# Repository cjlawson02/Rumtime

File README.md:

# Rumtime

**Rumtime** is a modular cocktail execution engine: ingredients are registered as services, recipes are resolved at runtime, and beverages are dispensed through a scalable ESP32-powered pump architecture.

This repo holds Rumtime documentation, Phase 0 bench-rig firmware, and KiCad PCB specifications. CAD and full product firmware are still in progress. The v1 hardware design uses food-safe tubing, Kamoer KPHM100-class reversible peristaltic pumps, modular 4-pump cartridges, and an ESP32-S3 controller. Software stack direction (Cloudflare kiosk UI, ESP32 dispense engine) and **locked** firmware runtime model (`ControlTask` + command queue on FreeRTOS) are in [`docs/16-firmware-and-software-architecture.md`](docs/16-firmware-and-software-architecture.md). Kiosk UX and **React + shadcn** stack in [`docs/17-kiosk-ui-plan.md`](docs/17-kiosk-ui-plan.md); production app at [`ui/kiosk/`](ui/kiosk/). Provisional device HTTP contract in [`docs/18-kiosk-device-api.md`](docs/18-kiosk-device-api.md).

## Current design snapshot

- **Version 1 pump count:** 8 installed pumps.
- **Expansion target:** 12 total pumps via one additional 4-pump module.
- **Control platform:** ESP32-S3 or similar ESP32 board, Wi-Fi only.
- **Pump strategy:** One reversible peristaltic pump per ingredient.
- **Measurement strategy:** Timed dispensing after calibration; **load cell required** for glass/ice detection, **flow-gated pour start**, and sanity checks.
- **Carbonation:** Do not pump carbonated mixers in v1. Software should instruct the user to top off manually.
- **Cleaning:** Moderate-effort cleaning with warm-water flush and Star San/session sanitizer workflow.
- **Budget target:** About $500 max for v1, excluding liquor and ingredients.
- **Build style:** Finished-looking countertop dispenser, with external bottles and replaceable tubing.

## Document map

| File                                                                                     | Purpose                                                                                        |
| ---------------------------------------------------------------------------------------- | ---------------------------------------------------------------------------------------------- |
| [`AGENTS.md`](AGENTS.md)                                                                 | Coding-agent and contributor behavior rules based on the requested Karpathy-style guidelines.  |
| [`docs/00-project-brief.md`](docs/00-project-brief.md)                                   | Scope, goals, assumptions, and non-goals.                                                      |
| [`docs/01-decisions.md`](docs/01-decisions.md)                                           | All captured design decisions from the planning conversation.                                  |
| [`docs/02-system-architecture.md`](docs/02-system-architecture.md)                       | Hardware architecture and module layout.                                                       |
| [`docs/03-parts-list-bom.md`](docs/03-parts-list-bom.md)                                 | Initial parts list with budget notes and sourcing guidance.                                    |
| [`docs/04-plumbing-and-fluid-path.md`](docs/04-plumbing-and-fluid-path.md)               | Tubing, fittings, bottles, nozzles, and ingredient compatibility.                              |
| [`docs/05-electronics-and-pcb.md`](docs/05-electronics-and-pcb.md)                       | Electrical design and 4-pump PCB guidance.                                                     |
| [`docs/06-flow-calibration-and-inventory.md`](docs/06-flow-calibration-and-inventory.md) | Timed flow calibration, flow-gated dispense, load cell, and inventory tracking.                |
| [`docs/07-cleaning-and-food-safety.md`](docs/07-cleaning-and-food-safety.md)             | Cleaning workflow, sanitizer handling, and maintenance assumptions.                            |
| [`docs/08-mechanical-design.md`](docs/08-mechanical-design.md)                           | Enclosure, pump cartridges, drip tray, nozzle cluster, and fridge notes.                       |
| [`docs/09-build-plan-and-verification.md`](docs/09-build-plan-and-verification.md)       | Staged build plan with success criteria and test checks.                                       |
| [`docs/10-open-questions-and-v2.md`](docs/10-open-questions-and-v2.md)                   | Deferred decisions, v2 ideas, and risks.                                                       |
| [`docs/11-sourcing-notes.md`](docs/11-sourcing-notes.md)                                 | Sourcing notes and search terms for pumps, tubing, fittings, electronics, and enclosure parts. |
| [`docs/12-phase-0-decisions.md`](docs/12-phase-0-decisions.md)                           | Research-backed Phase 0 part decisions (pump, PSU, KiCad).                                     |
| [`docs/13-phase-0-mini-bom.md`](docs/13-phase-0-mini-bom.md)                             | Phase 0 shopping list (~2-pump bench rig).                                                     |
| [`docs/14-bench-test-protocol.md`](docs/14-bench-test-protocol.md)                       | Bench tests, pass criteria, and session log template.                                          |
| [`docs/15-project-timeline.md`](docs/15-project-timeline.md)                             | Gantt chart, milestones, and procurement log (order/receive dates).                            |
| [`docs/16-firmware-and-software-architecture.md`](docs/16-firmware-and-software-architecture.md) | Software stack decisions, firmware layers, sequence runner, NVS ownership, migration from bench rig. |
| [`docs/17-kiosk-ui-plan.md`](docs/17-kiosk-ui-plan.md)                                   | Locked kiosk UX, connectivity, and guest/setup flows.                                          |
| [`ui/kiosk/`](ui/kiosk/)                                                                 | Production kiosk PWA — see [`ui/kiosk/README.md`](ui/kiosk/README.md). |
| [`firmware/bench-rig/`](firmware/bench-rig/)                                             | ESP32-S3 + TB6612 bring-up firmware (PlatformIO).                                              |
| [`firmware/controller/`](firmware/controller/)                                          | ESP32-S3 product firmware scaffold (`ControlTask` runtime; pump subsystem implemented).        |
| [`hardware/kicad/`](hardware/kicad/)                                                     | KiCad 4-pump module project, schematic spec, and `kicad-cli` scripts.                          |
| [`hardware/cad/`](hardware/cad/)                                                         | build123d parametric CAD (`src/`), dimension refs (`refs/`), export scripts; Onshape for assembly review only. |

## Design philosophy

Build the simplest version of Rumtime that can make repeatable drinks, clean up reasonably, and expand without rewiring everything. Avoid premature complexity such as inline flow meters, shared manifolds, fridge drilling, carbonated pumping, or fully custom embedded module networks until the basic 8-pump machine has been validated.

## Current status

**Next action:** Fit-check/measure the assembled load-cell cantilever, then solder the bar to HX711 (E+/E−/A+/A−) and run Tests 7–9. **Parallel:** finish 4-pump **PCB layout** (silkscreen/placement). Schematic v1 is ERC-clean. Bar **75 mm**, holes **5 / 15 / 59 / 69**, **M4 tapped** — [`hardware/cad/refs/estardyn-load-cell.md`](hardware/cad/refs/estardyn-load-cell.md). HX711↔MCU already wired (GPIO 8/9). Sessions: [06](docs/bench-results/2026-08-16-session-06.md) (measure + print) · [07](docs/bench-results/2026-08-16-session-07.md) (assembled, not measured).

**Done so far:** **8× correct 12 V HB pumps are on hand** and the 2 wrong 24 V units were returned. **P1 + P2** are bench-validated @ **1.75 ml/s**; dual-pump **~0.4 A**; anti-drip **100 ms**; P2 sequential 50 ml target → **~45 ml** (anti-drip); host CLI **`benchctl.py`** + proto=2 serial parser. The other 6 pumps still need incoming inspection and variance testing.

Decisions are locked in [`docs/12-phase-0-decisions.md`](docs/12-phase-0-decisions.md) (KPHM100-HBB10 pump, TB6612 breakout, ESP32-S3-DevKitC-1, KiCad for Phase 2 PCB).

## First prototype goal

Validate the core liquid path with 2–4 pumps. **Module schematic v1 is done** (ERC clean). Layout/silkscreen in progress. **Fab** waits on **DRC** (I2C bring-up is Test 10 on the first board).

1. Dispense 15 ml, 30 ml, and 60 ml targets by time after calibration.
2. Validate **flow-gated dispense** vs timed-only on de-primed and post–anti-drip lines (Test 9) — v1 pour default, not a PCB gate.
3. Reverse briefly after pours to reduce drips; document sequential pour drift (Test 4b).
4. Flush simple syrup and grenadine adequately with warm water.
5. Confirm tubing and nozzles do not retain obvious flavor or clog during a normal session.
6. Confirm load cell detects glass, ice tare, flow onset, and no-flow conditions (Tests 7–9) — v1 pour, not a PCB gate.
7. I2C pump control is proven on the **first assembled module** (Test 10), not a pre-fab MCP23017 breakout.

After DRC, fabricate the 4-pump module (`hardware/kicad/`) and proceed to the finished enclosure.

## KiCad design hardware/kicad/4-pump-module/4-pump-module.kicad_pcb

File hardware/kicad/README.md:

# KiCad Hardware

Rumtime PCBs are designed in **KiCad 10**. Bench validation (Phase 0–1) uses breakouts; the first custom board is the **4-pump module** (Phase 2).

Installed on this machine: **KiCad 10.0.5** (`kicad-cli` on PATH via Homebrew).

## Repo layout

```text
hardware/kicad/
  README.md
  4-pump-module-spec.md     — nets, pin map, safe-off (source of truth before symbols)
  4-pump-module/            — KiCad project
  main-controller-spec.md   — motherboard nets / connectors
  main-controller/          — KiCad project
    Rumtime.pretty/           — local footprints (Mini560)
    fp-lib-table
  scripts/
    check.sh                — ERC (+ DRC); default both boards
    export.sh               — PDF / netlist / BOM; --fab for Gerbers
  out/                      — generated (gitignored)
```

## Agent / CLI hook

`kicad-cli` cannot place symbols. Use it to **check and export** after schematic/layout edits in KiCad.

```bash
kicad-cli version
hardware/kicad/scripts/check.sh                       # ERC both boards
hardware/kicad/scripts/check.sh main-controller       # one board
hardware/kicad/scripts/check.sh --drc                 # ERC + DRC (after Edge.Cuts)
hardware/kicad/scripts/export.sh                      # PDF + netlist
hardware/kicad/scripts/export.sh --fab                # Gerbers + drill + STEP
```

Useful one-shots:

```bash
kicad-cli sch erc --exit-code-violations hardware/kicad/4-pump-module/4-pump-module.kicad_sch
kicad-cli sch erc --exit-code-violations hardware/kicad/main-controller/main-controller.kicad_sch
kicad-cli pcb drc --schematic-parity --exit-code-violations hardware/kicad/4-pump-module/4-pump-module.kicad_pcb
kicad-cli sch export pdf --output hardware/kicad/out/sch.pdf hardware/kicad/4-pump-module/4-pump-module.kicad_sch
```

Open the GUI:

```bash
open -a KiCad hardware/kicad/4-pump-module/4-pump-module.kicad_pro
open -a KiCad hardware/kicad/main-controller/main-controller.kicad_pro
```

## Design sequence

| Phase | Board                      | Action                                              |
| ----- | -------------------------- | --------------------------------------------------- |
| 0–1   | None                       | TB6612 breakout on breadboard; HX711 + load cell    |
| 2     | 4-pump module              | First fab — Test 10 I2C bring-up on this board      |
| 4     | Second 4-pump module       | Duplicate validated design                          |
| 5     | Main controller            | PCB ordered 2026-10-29. DevKit socketed. |

Fill schematic sheets per [`4-pump-module-spec.md`](4-pump-module-spec.md) / [`main-controller-spec.md`](main-controller-spec.md). **4-pump** PCB ordered 2026-10-25 (OSH Park). **Main-controller** PCB ordered 2026-10-29. Commit `.kicad_pro` / `.kicad_sch` / `.kicad_pcb` — not `out/` or `*-backups/`.

## Gate before fabrication

HX711 / load cell is on the **ESP32 controller**, not this module. Tests 7–9 do **not** gate schematic or fab.

Do not **order** boards until:

1. Measured pump current (dry and wet stall) recorded in `docs/bench-results/`. _(Done — TB6612 OK.)_
2. `scripts/check.sh` ERC (and DRC) clean. _(ERC done 2026-08-16; DRC after Edge.Cuts.)_
3. Schematic safe-off review (Test 10.4: IN1/IN2 PDs, STBY PD, PWM strap, MCP23017 /RESET).

**Do not** wait on an MCP23017 breakout. Test 10.1–10.3 run on the first assembled module.

Layout may continue now. Phase 1 pour completeness (Tests 4, 6, 7–9, P3) is parallel v1 work — see [`docs/14-bench-test-protocol.md`](../../docs/14-bench-test-protocol.md).

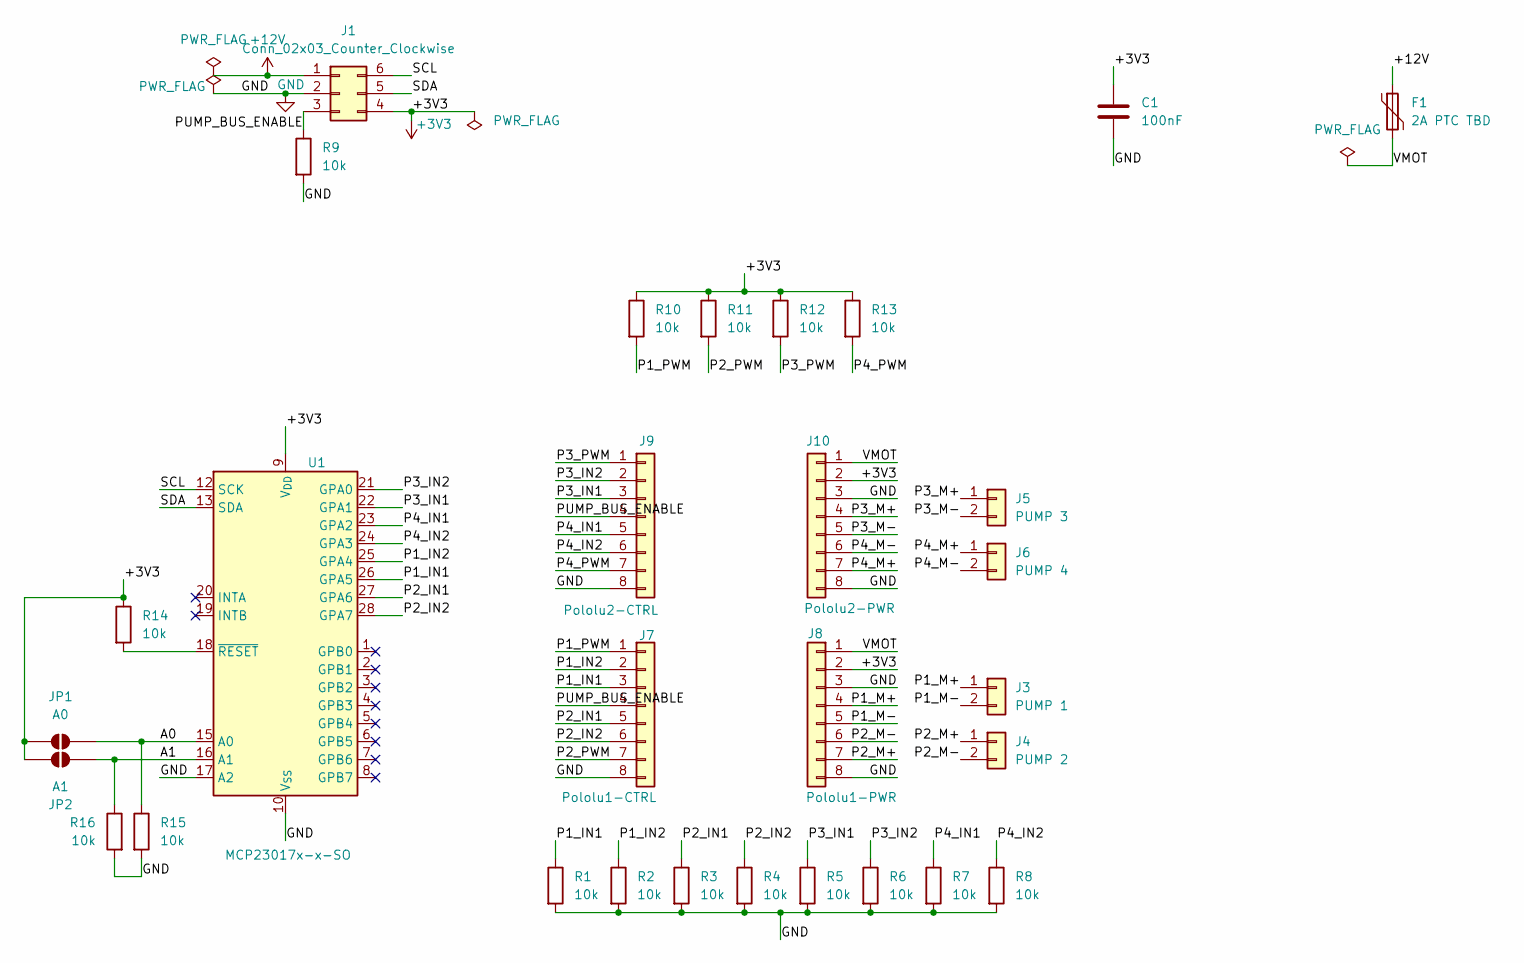
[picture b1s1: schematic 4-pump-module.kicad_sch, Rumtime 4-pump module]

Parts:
C1: 100nF; C_0805_2012Metric_Pad1.18x1.45mm_HandSolder
F1: 2A PTC TBD; Fuse_1812_4532Metric_Pad1.30x3.40mm_HandSolder
J1: Conn_02x03_Counter_Clockwise; Molex_Micro-Fit_3.0_43045-0600_2x03_P3.00mm_Horizontal
J3: PUMP 1; JST_XH_B2B-XH-A_1x02_P2.50mm_Vertical
J4: PUMP 2; JST_XH_B2B-XH-A_1x02_P2.50mm_Vertical
J5: PUMP 3; JST_XH_B2B-XH-A_1x02_P2.50mm_Vertical
J6: PUMP 4; JST_XH_B2B-XH-A_1x02_P2.50mm_Vertical
J7: Pololu1-CTRL; PinSocket_1x08_P2.54mm_Vertical
J8: Pololu1-PWR; PinSocket_1x08_P2.54mm_Vertical
J9: Pololu2-CTRL; PinSocket_1x08_P2.54mm_Vertical
J10: Pololu2-PWR; PinSocket_1x08_P2.54mm_Vertical
JP1: A0; SolderJumper-2_P1.3mm_Open_Pad1.0x1.5mm
JP2: A1; SolderJumper-2_P1.3mm_Open_Pad1.0x1.5mm
R1, R2, R3, R4, R5, R6, R7, R8, R9, R10, R11, R12, R13, R14, R15, R16: 10k; R_0805_2012Metric_Pad1.20x1.40mm_HandSolder
U1: MCP23017x-x-SO; SOIC-28W_7.5x17.9mm_P1.27mm

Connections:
+3V3: C1.1, J1.4, J8.2, J10.2, JP1.1 (A), JP2.1 (A), R10.1, R11.1, R12.1, R13.1, R14.1, U1.9 (V_{DD})
+12V: F1.1, J1.1
/A0: JP1.2 (B), R15.1, U1.15 (A0)
/A1: JP2.2 (B), R16.1, U1.16 (A1)
/P1_IN1: J7.3, R1.1, U1.26 (GPA5)
/P1_IN2: J7.2, R2.1, U1.25 (GPA4)
/P1_M+: J3.1, J8.4
/P1_M-: J3.2, J8.5
/P1_PWM: J7.1, R10.2
/P2_IN1: J7.5, R3.1, U1.27 (GPA6)
/P2_IN2: J7.6, R4.1, U1.28 (GPA7)
/P2_M+: J4.1, J8.7
/P2_M-: J4.2, J8.6
/P2_PWM: J7.7, R11.2
/P3_IN1: J9.3, R5.1, U1.22 (GPA1)
/P3_IN2: J9.2, R6.1, U1.21 (GPA0)
/P3_M+: J5.1, J10.4
/P3_M-: J5.2, J10.5
/P3_PWM: J9.1, R12.2
/P4_IN1: J9.5, R7.1, U1.23 (GPA2)
/P4_IN2: J9.6, R8.1, U1.24 (GPA3)
/P4_M+: J6.1, J10.7
/P4_M-: J6.2, J10.6
/P4_PWM: J9.7, R13.2
/PUMP_BUS_ENABLE: J1.3, J7.4, J9.4, R9.1
/SCL: J1.6, U1.12 (SCK)
/SDA: J1.5, U1.13 (SDA)
/VMOT: F1.2, J8.1, J10.1
GND: C1.2, J1.2, J7.8, J8.3, J8.8, J9.8, J10.3, J10.8, R1.2, R2.2, R3.2, R4.2, R5.2, R6.2, R7.2, R8.2, R9.2, R15.2, R16.2, U1.10 (V_{SS}), U1.17 (A2)
unnamed: R14.2, U1.18 (~RESET)

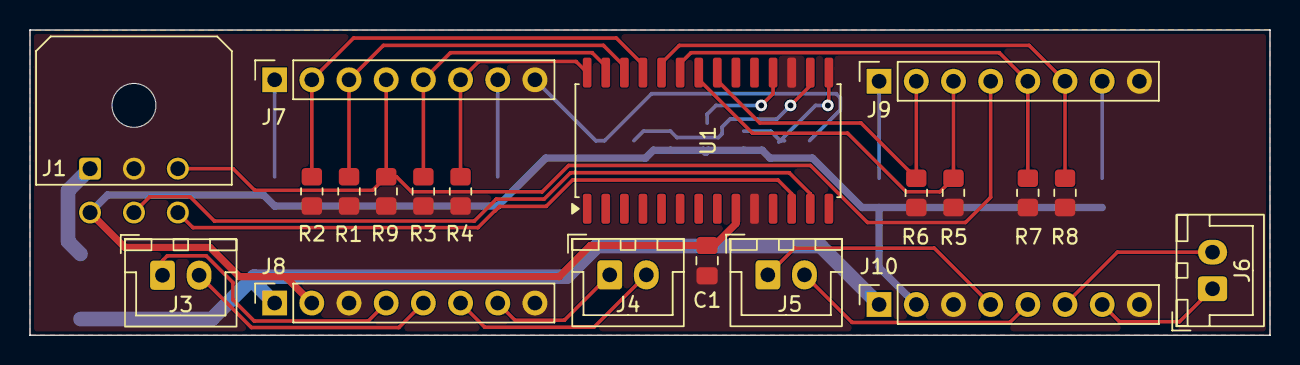
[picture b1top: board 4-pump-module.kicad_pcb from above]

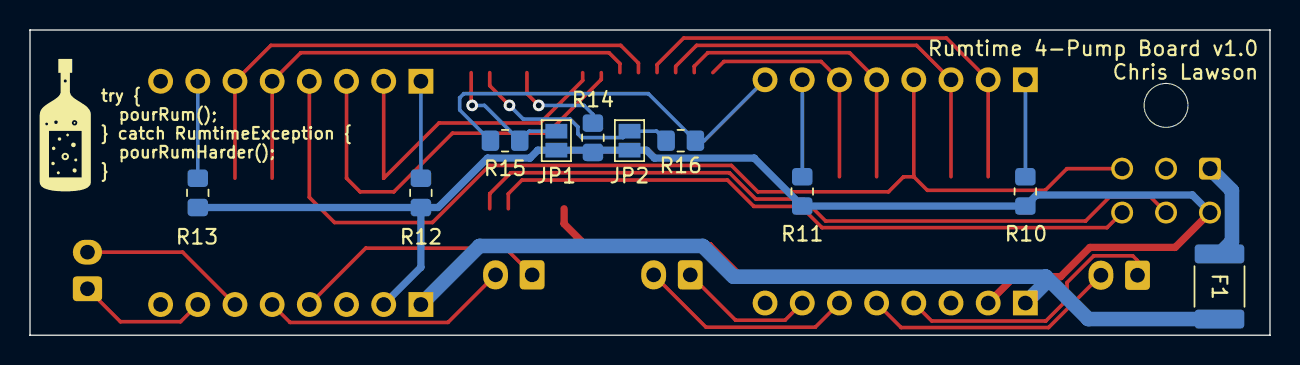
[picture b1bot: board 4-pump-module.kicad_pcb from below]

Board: 2 copper layers, 84.7 x 20.9 mm, 30 parts (10 on the bottom side), 30 nets.

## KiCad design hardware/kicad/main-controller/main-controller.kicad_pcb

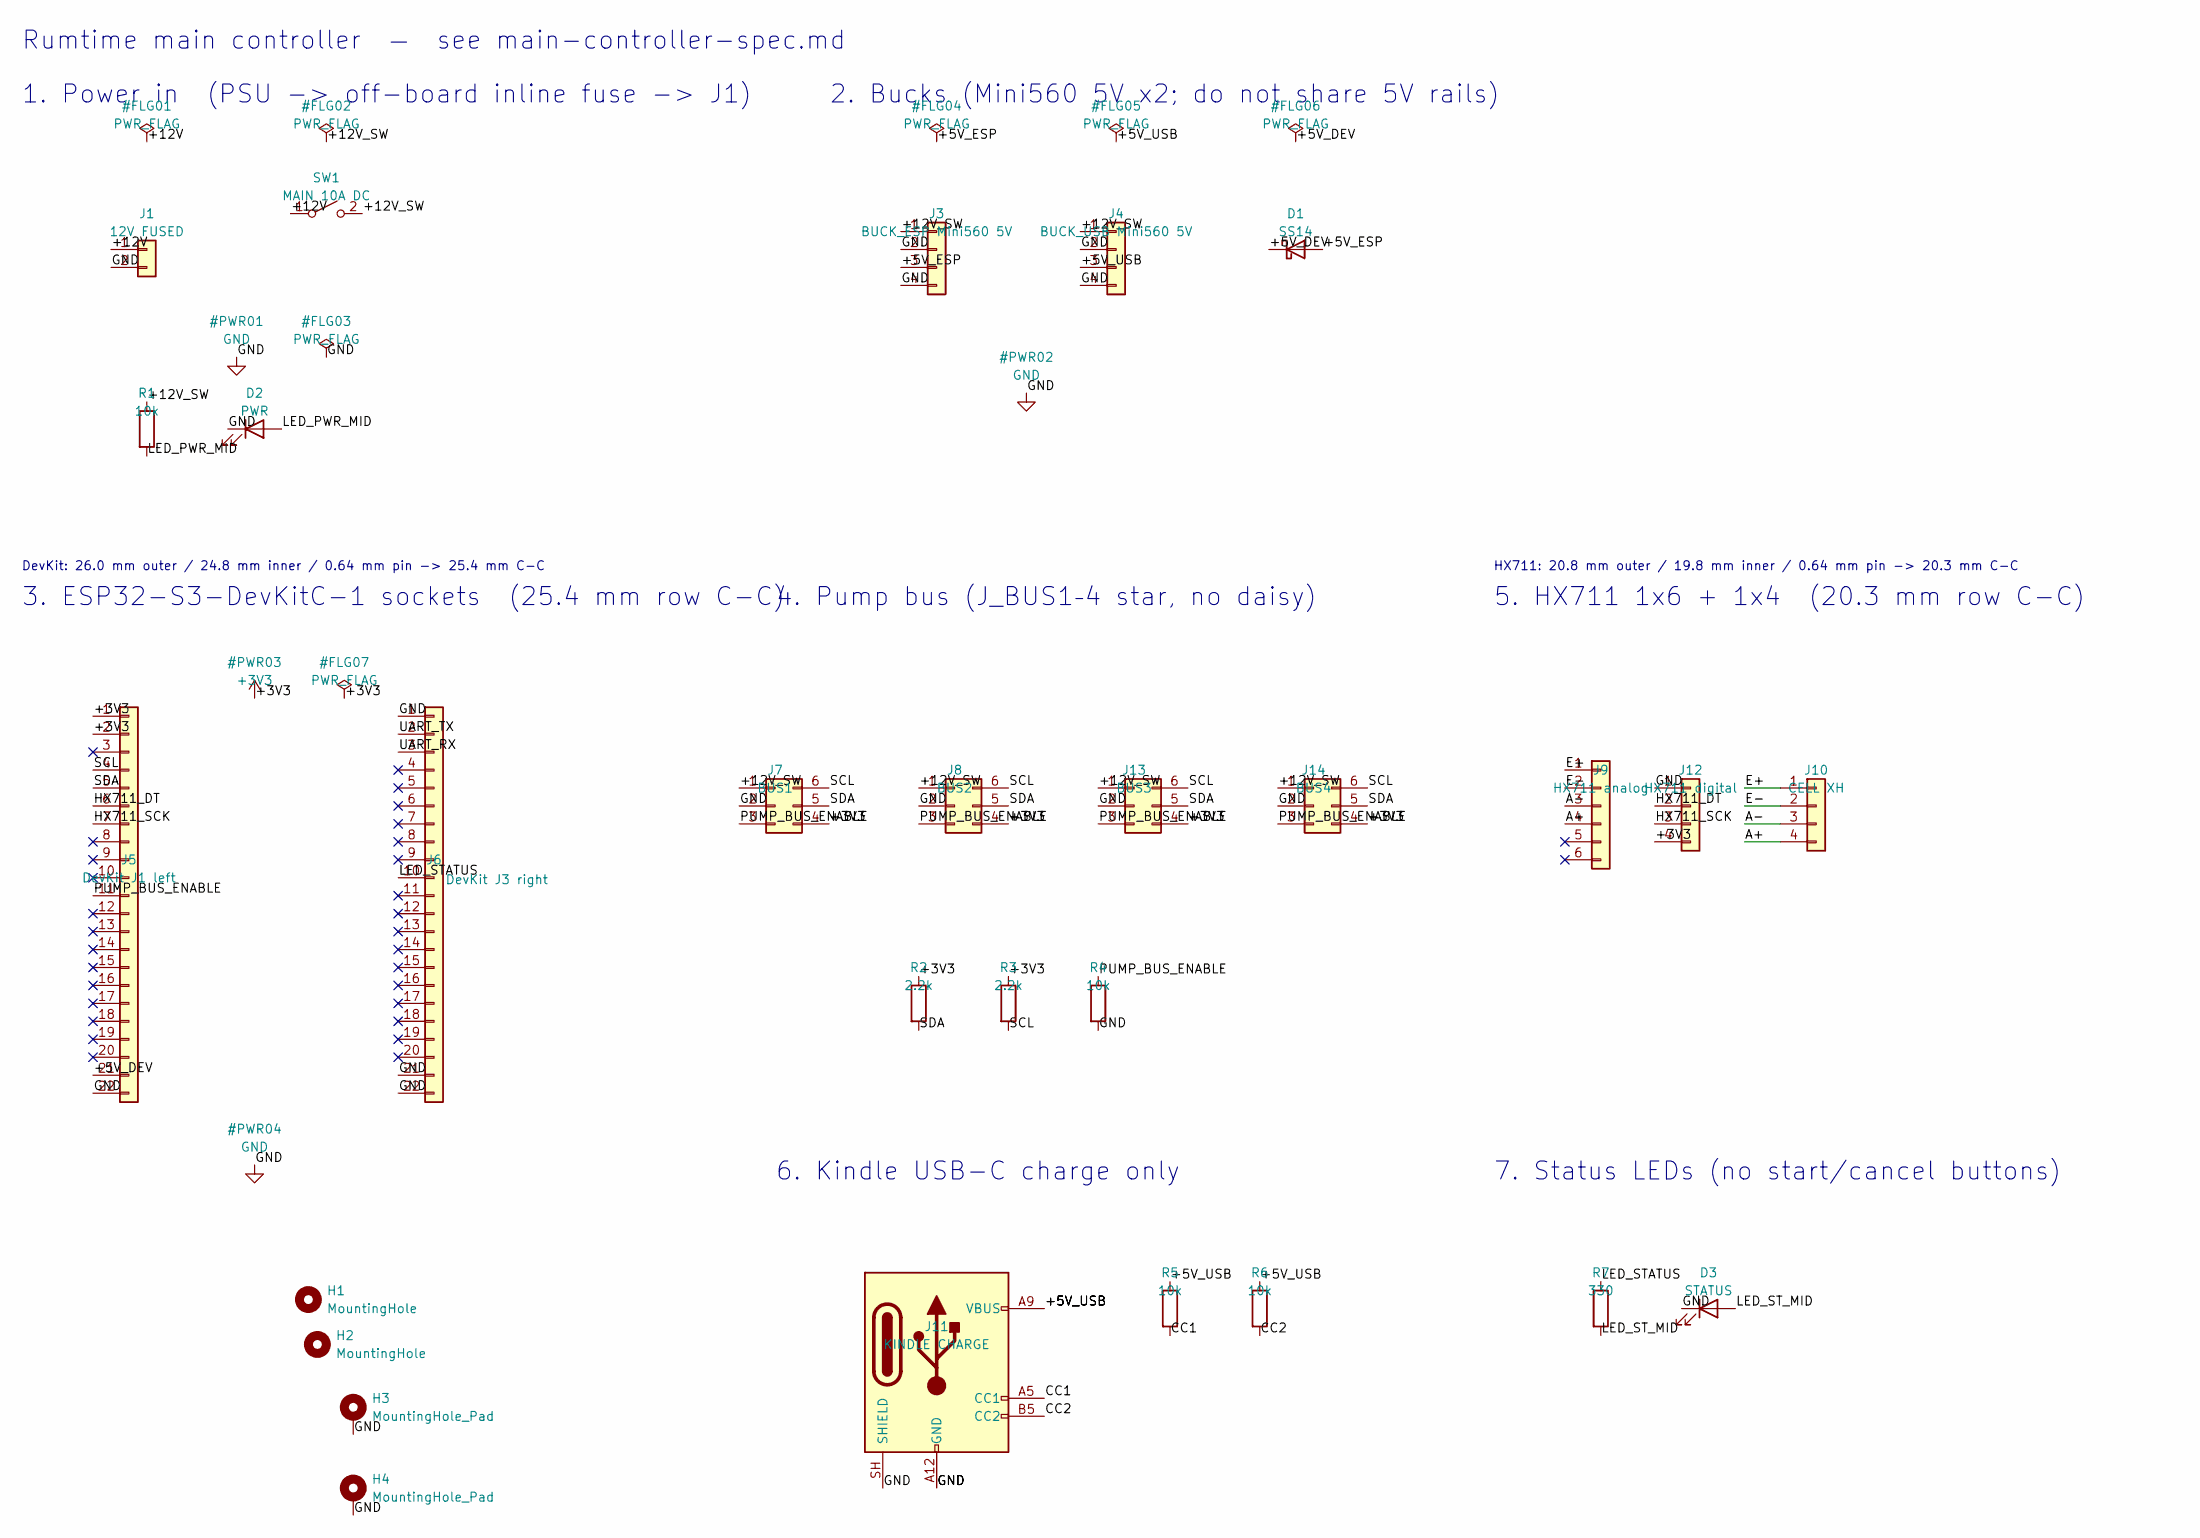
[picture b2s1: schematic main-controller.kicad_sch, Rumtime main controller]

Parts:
D1: SS14; D_SMA
D2: PWR; LED_D3.0mm
D3: STATUS; LED_D3.0mm
H1, H2: MountingHole; MountingHole_3.2mm_M3
H3, H4: MountingHole_Pad; MountingHole_3.2mm_M3_Pad
J1: 12V FUSED; TerminalBlock_Phoenix_MKDS-1,5-2-5.08_1x02_P5.08mm_Horizont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
J3: BUCK_ESP Mini560 5V; Mini560
J4: BUCK_USB Mini560 5V; Mini560
J5: DevKit J1 left; PinSocket_1x22_P2.54mm_Vertical
J6: DevKit J3 right; PinSocket_1x22_P2.54mm_Vertical
J7: BUS1; Molex_Micro-Fit_3.0_43045-0612_2x03_P3.00mm_Vertical
J8: BUS2; Molex_Micro-Fit_3.0_43045-0612_2x03_P3.00mm_Vertical
J9: HX711 analog; PinSocket_1x06_P2.54mm_Vertical
J10: CELL XH; JST_XH_B4B-XH-A_1x04_P2.50mm_Vertical
J11: KINDLE CHARGE; USB_C_Receptacle_GCT_USB4125-xx-x-0190_6P_TopMnt_Horizontal
J12: HX711 digital; PinSocket_1x04_P2.54mm_Vertical
J13: BUS3; Molex_Micro-Fit_3.0_43045-0612_2x03_P3.00mm_Vertical
J14: BUS4; Molex_Micro-Fit_3.0_43045-0612_2x03_P3.00mm_Vertical
R1, R4, R5, R6: 10k; R_0805_2012Metric
R2, R3: 2.2k; R_0805_2012Metric
R7: 330; R_0805_2012Metric
SW1: MAIN 10A DC; TerminalBlock_Phoenix_MKDS-1,5-2-5.08_1x02_P5.08mm_Horizont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

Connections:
+3V3: J5.1, J5.2, J7.4, J8.4, J12.4, J13.4, J14.4, R2.1, R3.1
/+5V_DEV: D1.1 (K), J5.21
/+5V_ESP: D1.2 (A), J3.3
/+5V_USB: J4.3, J11.A9 (VBUS), J11.B9 (VBUS), R5.1, R6.1
/+12V: J1.1, SW1.1 (A)
/+12V_SW: J3.1, J4.1, J7.1, J8.1, J13.1, J14.1, R1.1, SW1.2 (B)
/A+: J9.4, J10.4
/A-: J9.3, J10.3
/CC1: J11.A5 (CC1), R5.2
/CC2: J11.B5 (CC2), R6.2
/E+: J9.1, J10.1
/E-: J9.2, J10.2
/HX711_DT: J5.6, J12.2
/HX711_SCK: J5.7, J12.3
/LED_PWR_MID: D2.2 (A), R1.2
/LED_STATUS: J6.10, R7.1
/LED_ST_MID: D3.2 (A), R7.2
/PUMP_BUS_ENABLE: J5.11, J7.3, J8.3, J13.3, J14.3, R4.1
/SCL: J5.4, J7.6, J8.6, J13.6, J14.6, R3.2
/SDA: J5.5, J7.5, J8.5, J13.5, J14.5, R2.2
/UART_RX: J6.3
/UART_TX: J6.2
GND: D2.1 (K), D3.1 (K), H3.1 (1_1), H4.1 (1_1), J1.2, J3.2, J3.4, J4.2, J4.4, J5.22, J6.1, J6.21, J6.22, J7.2, J8.2, J11.A12 (GND), J11.B12 (GND), J11.SH (SHIELD), J12.1, J13.2, J14.2, R4.2

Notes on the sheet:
Rumtime main controller — see main-controller-spec.md
2. Bucks (Mini560 5V x2; do not share 5V rails)
HX711: 20.8 mm outer / 19.8 mm inner / 0.64 mm pin -> 20.3 mm C-C
7. Status LEDs (no start/cancel buttons)
5. HX711 1x6 + 1x4 (20.3 mm row C-C)
4. Pump bus (J_BUS1–4 star, no daisy)
3. ESP32-S3-DevKitC-1 sockets (25.4 mm row C-C)
DevKit: 26.0 mm outer / 24.8 mm inner / 0.64 mm pin -> 25.4 mm C-C
6. Kindle USB-C charge only
1. Power in (PSU -> off-board inline fuse -> J1)

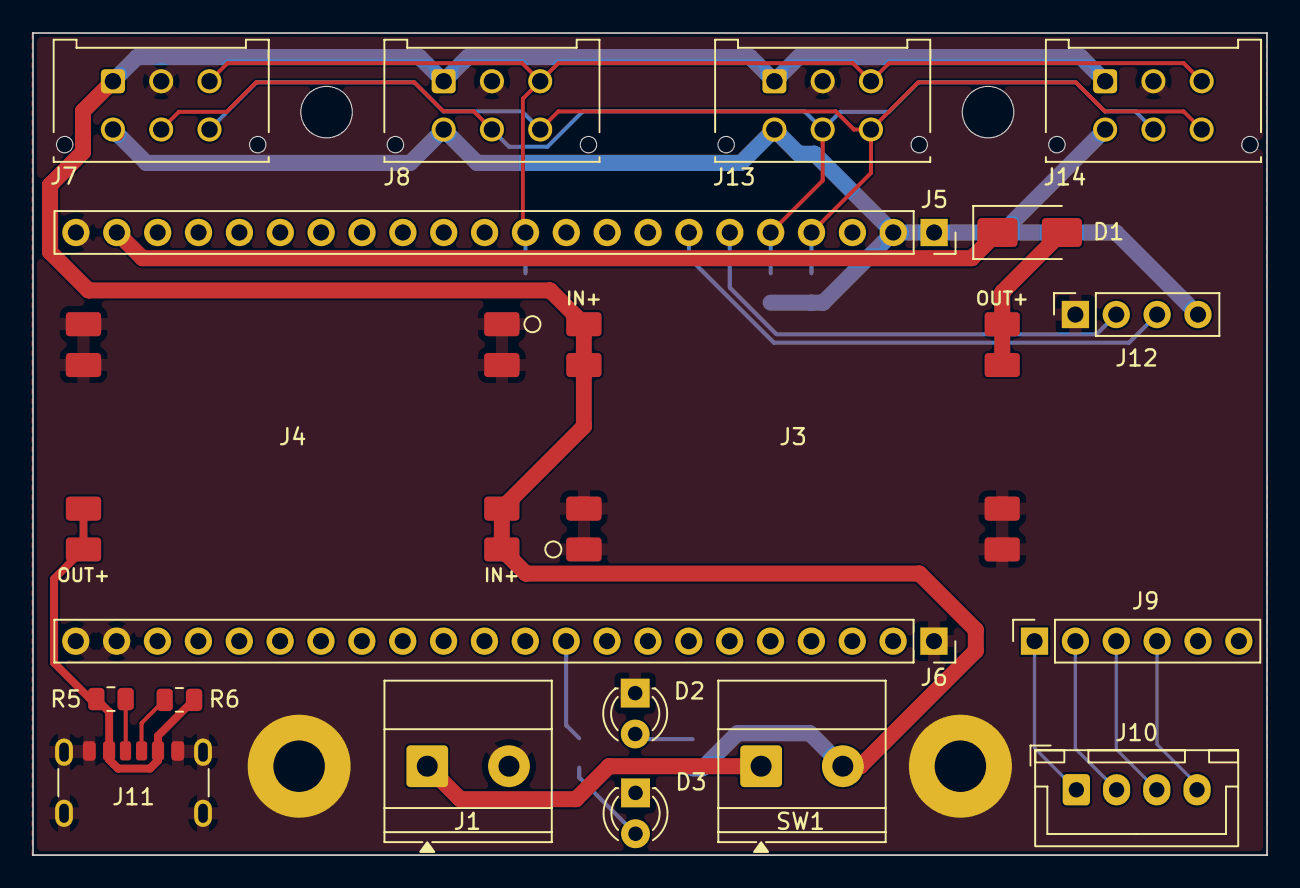
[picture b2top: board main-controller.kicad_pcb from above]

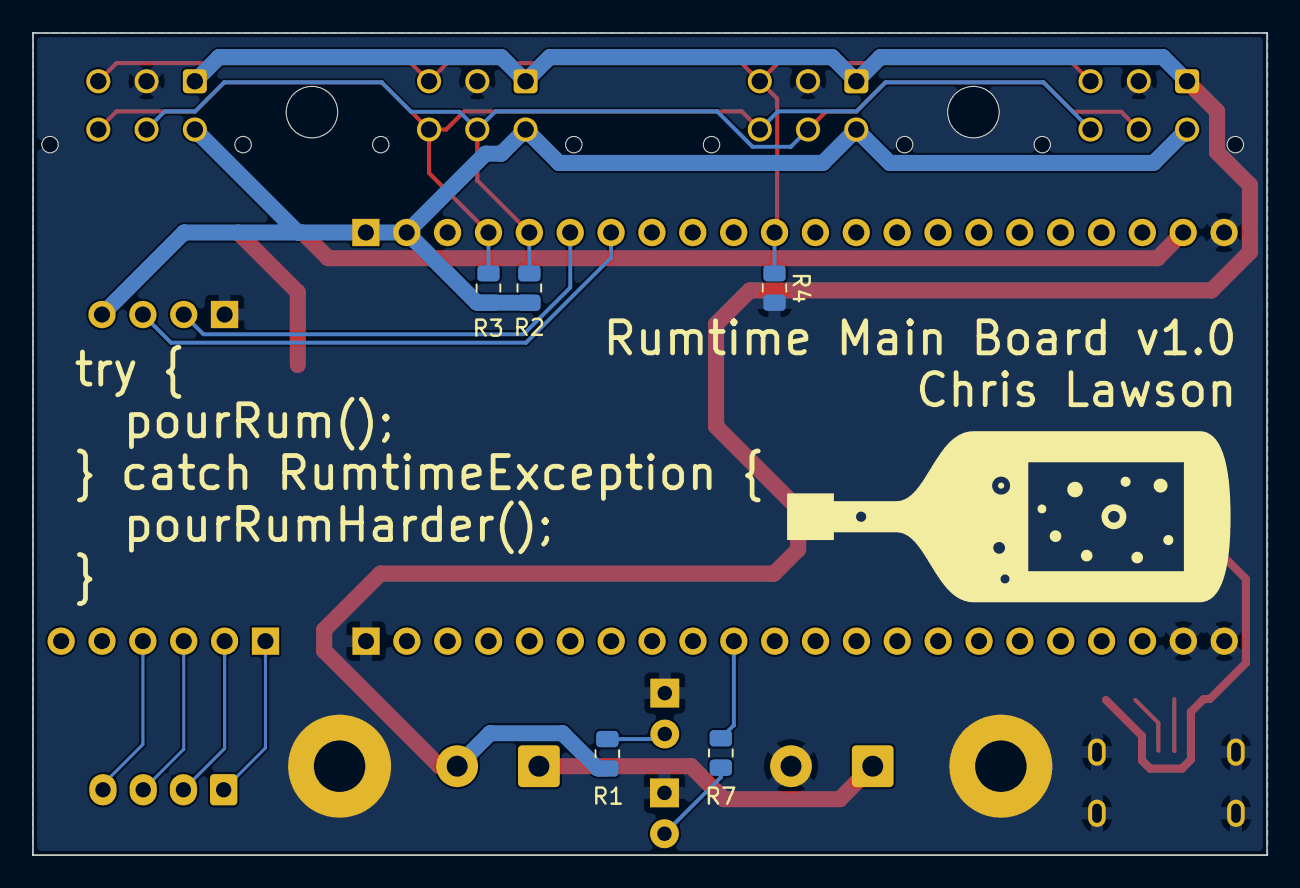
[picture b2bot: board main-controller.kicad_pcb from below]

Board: 2 copper layers, 76.7 x 51.1 mm, 28 parts (5 on the bottom side), 21 nets.

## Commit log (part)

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2026-06-21 Enhance documentation for Rumtime v1, emphasizing load cell requirements and flow-gated dispensing.
    Update AGENTS.md with guidelines for sourcing and part substitutions. Revise README.md to clarify measurement strategy, making load cell usage mandatory. Amend various documentation files to reflect 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
2026-06-21 Add CI workflow for bench-rig firmware build and artifact upload
    Create a GitHub Actions CI workflow to automate the build process for the bench-rig firmware. The workflow includes steps for checking out the code, caching PlatformIO dependencies, setting up Platfo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
